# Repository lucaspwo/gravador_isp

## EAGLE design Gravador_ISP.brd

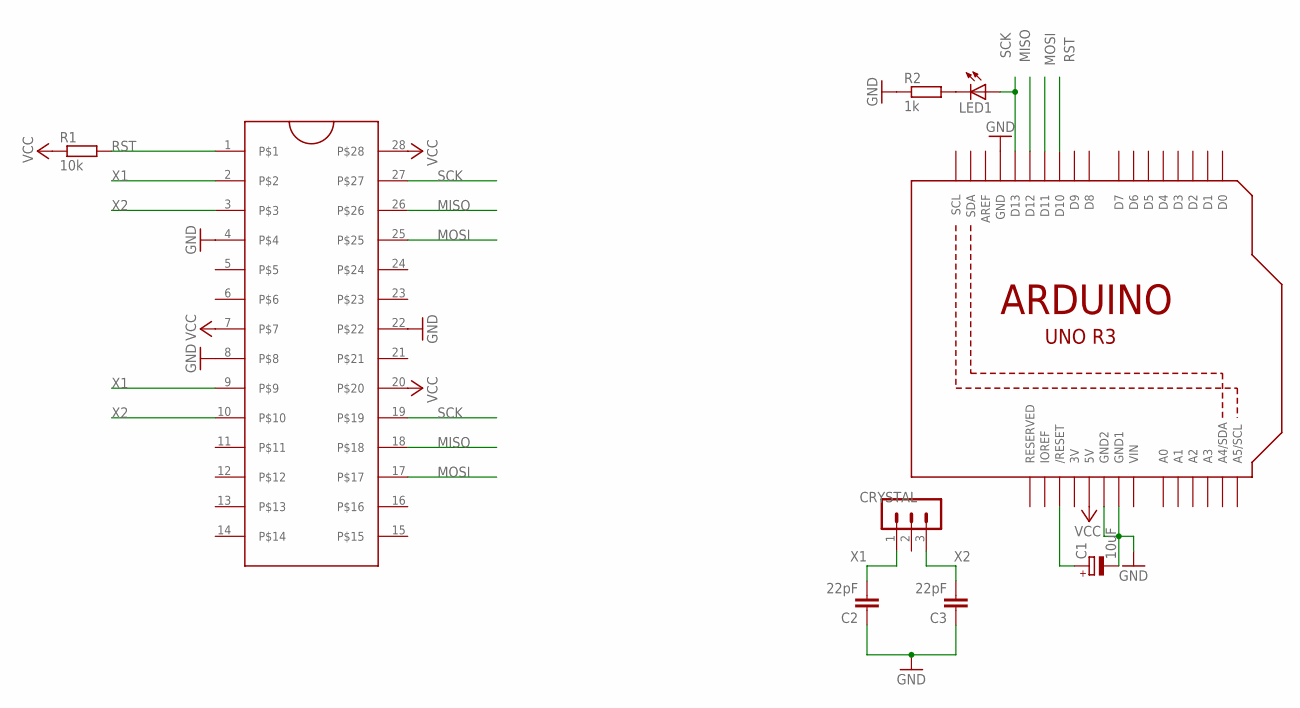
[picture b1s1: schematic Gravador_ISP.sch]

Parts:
C1: 10uF; E2,5-5
C2, C3: 22pF; C050-024X044
CRYSTAL: MA03-1
J1: ZIFSOCKET-28-3"; DIL28-3-ZIF_SOCKET
LED1: LED3MM
R1: 10k; 0207/10
R2: 1k; 0207/10
U1: ARDUINOR3-DIMENSION; ARDUINOR3

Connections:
3V: U1.3V
GND: C1.-, C2.1, C3.1, J1.4, J1.8, J1.22, R2.1, U1.GND, U1.GND1, U1.GND2
MISO: J1.18, J1.26, U1.D12
MOSI: J1.17, J1.25, U1.D11
unnamed: LED1.K (C), R2.2
unnamed: C1.+, U1.RESET (/RESET)
RST: J1.1, R1.2, U1.D10
SCK: J1.19, J1.27, LED1.A, U1.D13
VCC: J1.7, J1.20, J1.28, R1.1, U1.5V
VIN: U1.VIN
X1: C2.2, CRYSTAL.1, J1.2, J1.9
X2: C3.2, CRYSTAL.3, J1.3, J1.10

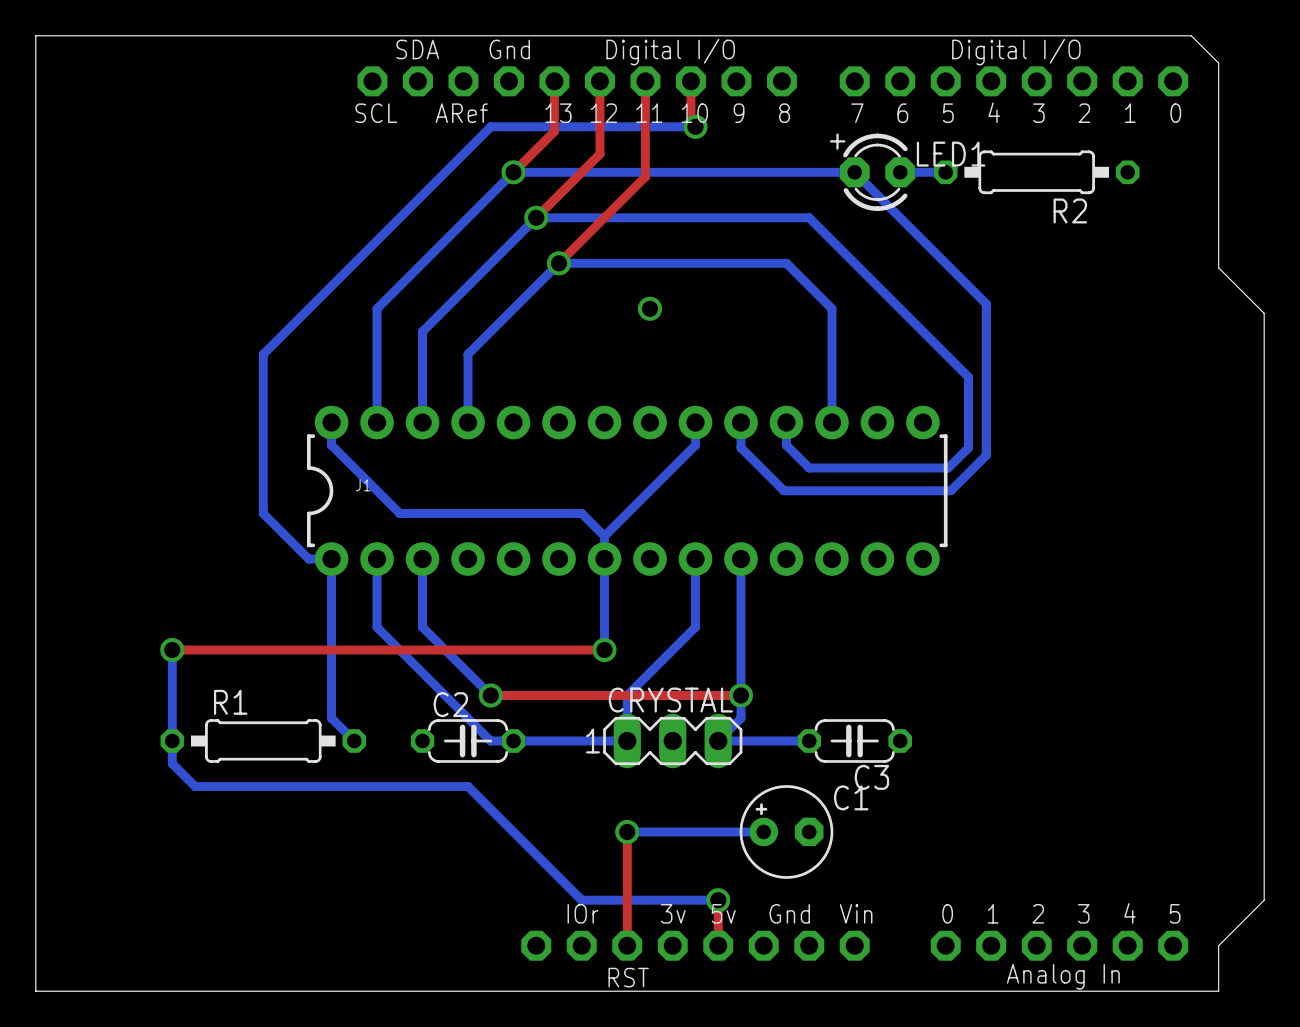
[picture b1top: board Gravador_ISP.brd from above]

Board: 2 copper layers, 68.6 x 53.3 mm, 9 parts (0 on the bottom side), 10 nets.

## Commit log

2020-02-24 commit inicial

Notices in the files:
parts and their libraries:
SparkFun-Connectors: Licensing: Creative Commons ShareAlike 4.0 International - https://creativecommons.org/licenses/by-sa/4.0
